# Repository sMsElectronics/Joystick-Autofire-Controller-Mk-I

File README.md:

# Joystick Auto Fire Controller V1.1
 ### This is a small form factor digitally controlled auto fire PCB with 0.1" connector headers for convenient installation into Commodore 64 and Atari Joysticks. It can be used to create custom DIY joysticks. Fire rates can be controlled using a potentiometer (analog mode) to smoothly transition from fire rate from 2 to 25 pulses per second (PPS). Alternatively, you can enter a fixed rates mode (digital Mode) with a series of button presses. The fixed rate selections are 5, 10, and 15 PPS. A normal mode is also possible by disabling the auto fire in both scenarios above. All feedback is displayed on an RGB WS2812B compatible LED and FIRE LED. Various colors and fade animation are displayed representing all the modes and rates. Further below, these modes and how to enter them are described in the illustrations

 ## *The complete and tested auto fire controller PCB's, complete with documentation, are available on my sMs Retro Electronics KoFi Shop*

## [sMs Retro Electronics KoFi Shop](https://ko-fi.com/smsretroelectronics)

 ## Size of board compared to the end of a pen.  

 ## PCB TOP VIEW

 ## PCB BOTTOM VIEW
### A convenient silkscreen showing signal names NOTE: SQUARE PIN = 1

# J2 Signal Definitions: 

|Pin Number|Signal Name|Description|
|:--:|:--:|:--|
|1|/FIRE OUT|Active low signal output that emulates the trigger into the C64 or other computer to auto fire a weapon. This signal is normally HIGH. Signal wires to pin 6 of a joystick: 
|2|FIRE_BUT|Signal from fire control button on joystick. This signal pulls LOW each time the joystick fire button is pressed. This signal is normally HIGH. :
|3|DIGRATESEL|Selects the auto fire rate. Rates of 5, 10 and 20 PPS are selectable. A Quick press cycles theSE rates. A long press FOR 1.5+ seconds enables the analog rate control|   
|4|ANA_RATE|A 0-5 VDC input from external 10K potentiometer to vary the fire rate from 2 to 23 pulses per second. This potentiometer input is only active if the joystick is set to smooth analog fire control|
|5|Fire LED-|output for user option to mount external led to indicate the press of the fire button in normal mode or to indicate auto fire pulsing in either of two auto fire modes|
|6|VCC|supply for LED+. No limiting resistor is required|
|7|DATA IN|External Neopixel RGB LED Data IN Signal|
|8|VCC|5V supply for Neopixel|
|9|GND|Ground connection for Neopixel|

# J1 Signal Definitions: 

|Pin Number|Signal Name|
|:--:|:--|
|1|5V IN|
|2|GROUND| 
   
# Summary of Modes

- Fixed Auto fire Mode
- Smooth or Analog Fire 
- Normal Mode
  
# How to Enter and Operate Each Mode

 <BR>

<BR>

# Typical application in a joystick design

# Joystick wiring details

The following diagram shows how to wire a Sanwah JLF-TP-8YT joystick , or compatible, assembly to a 9 PIN joystick cable. Some cables may be different in their color coding so its best to check continuity from each pin to the wires and identify the color verses pin. 

## If you want to DIY build your boards, the source files are available in the VS Code folder. Just keep in mind that when you create the project, inside the "libdeps" folder that contains the Tinbutton folder and TinyButton.cpp file. This file has been modifed to work with this project with the following changes. It was found that a long button press of 4 seconds was way too long and the long press woul dbe activated in 1.5 seconds instead.    

   ## Modification to file ***TinyButton.cpp*** to Shorten the LONG press criteria from 4 seconds to 1.5 seconds 
   ### W.Manganaro 2025
   
## FROM:    

      if ((currentMillis - _buttonPressTime) >= 4000)  
## TO:    

      //Value changed from 4000 to 1500 to validate a LONG press in a shorter time (approx 1.5 seconds)
      if ((currentMillis - _buttonPressTime) >= 1500)

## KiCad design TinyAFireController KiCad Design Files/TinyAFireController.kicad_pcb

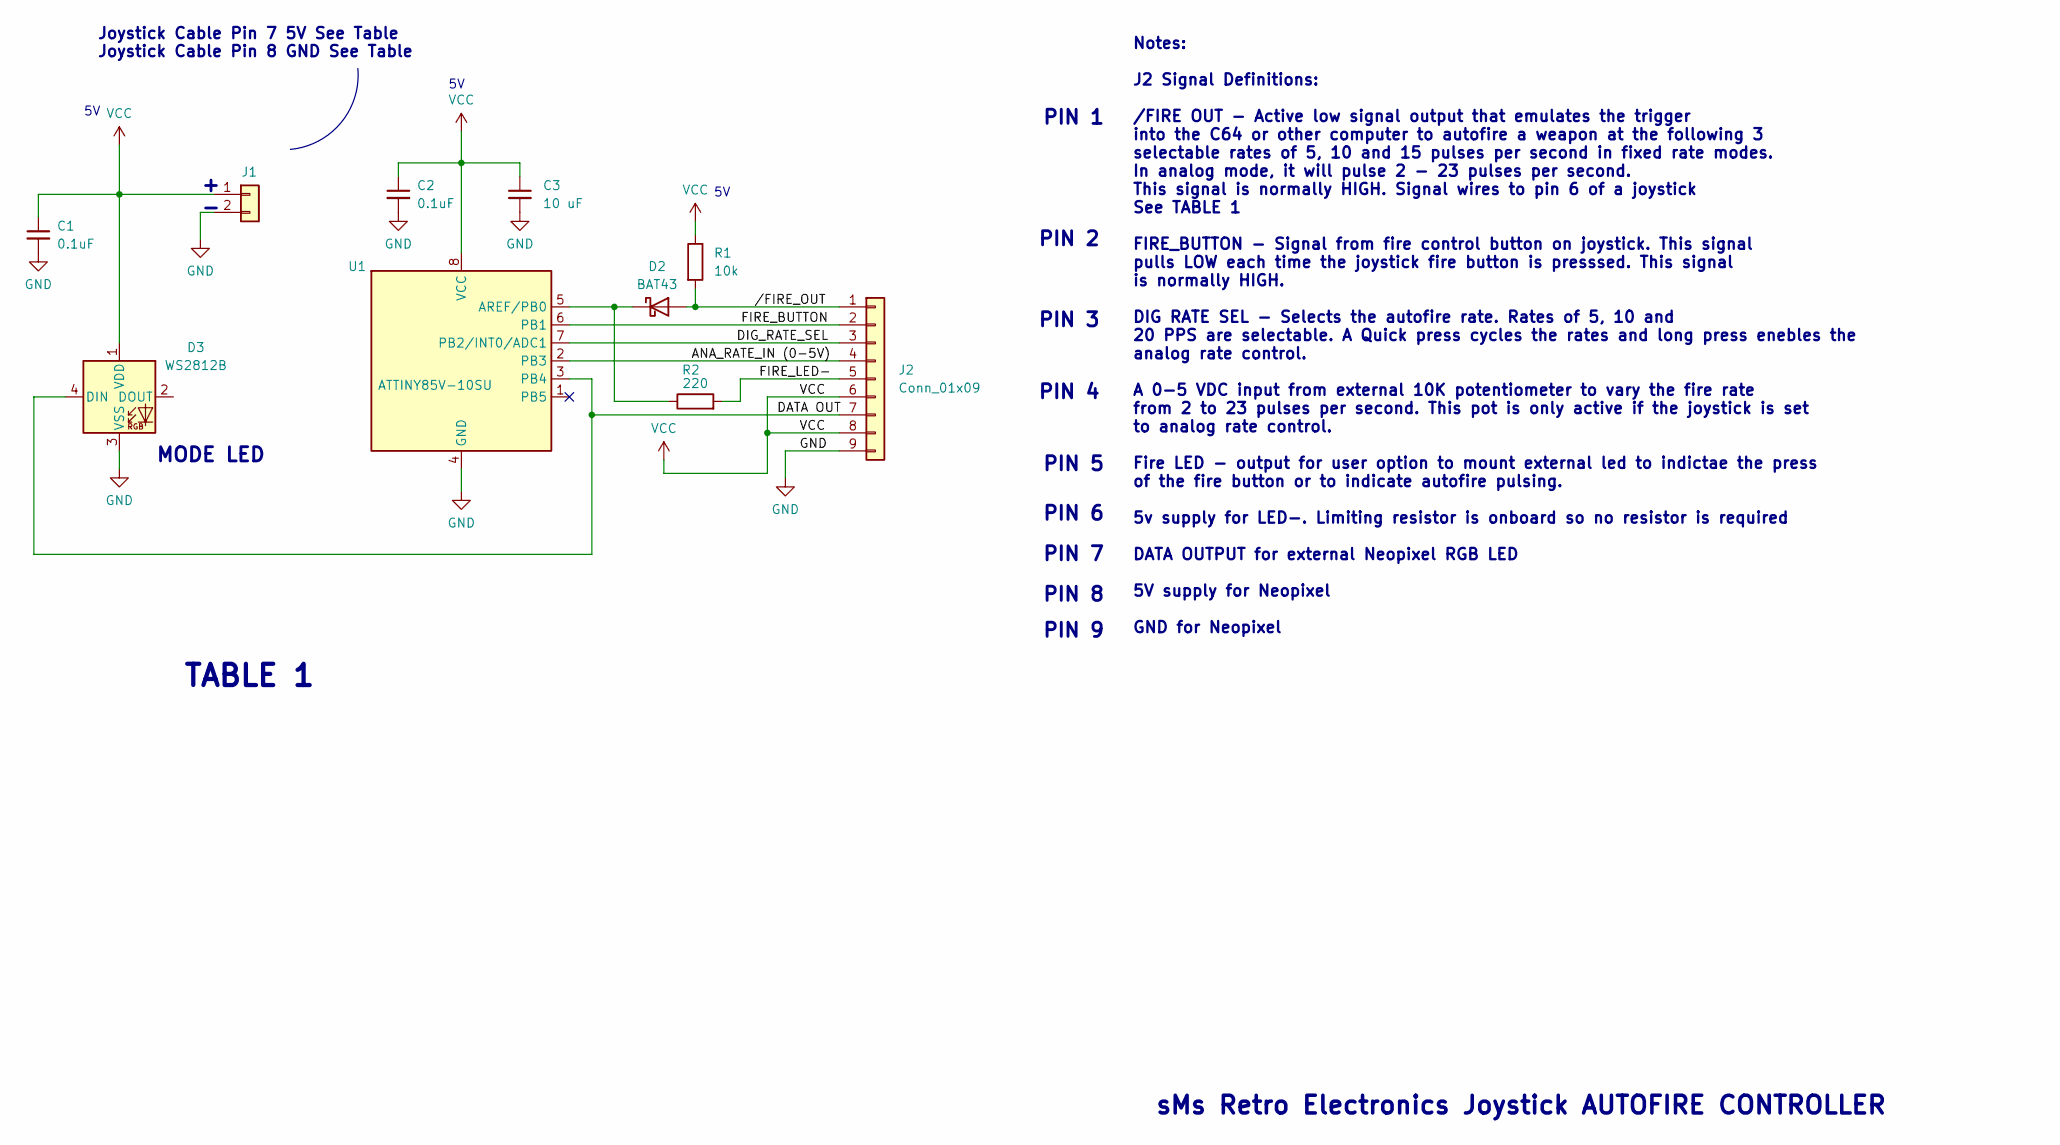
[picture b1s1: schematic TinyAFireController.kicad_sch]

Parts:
C1, C2, C3: 0.1uF_0603_16V; C_0805_2012Metric; Part Number 0603YC104KAT2A; JLCPCB ID C14663
D2: BAT43; D_SOD-123
D3: WS2812B; LED_WS2812B_PLCC4_5.0x5.0mm_P3.2mm
J1: Conn_01x02; PinHeader_1x02_P2.54mm_Horizontal; Part Number 1-0201FBV0T
J2: Conn_01x09; PinHeader_1x09_P2.54mm_Horizontal; Part Number 1-0901FBV0T
R1, R2: 100k_0603; R_0805_2012Metric; Part Number RC0603FR-07100KL; JLCPCB ID C25803
U1: ATTINY85V-10SU; SOIC-8W_5.3x5.3mm_P1.27mm

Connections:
/: D2.1 (K), R2.1, U1.5 (AREF/PB0)
/ANA_RATE_IN (0-5V): J2.4, U1.2 (PB3)
/DATA IN: D3.4 (DIN), J2.7, U1.3 (PB4)
/DIG_RATE_SEL: J2.3, U1.7 (PB2/INT0/ADC1)
/FIRE_BUTTON: J2.2, U1.6 (PB1)
/FIRE_LED-: J2.5, R2.2
//FIRE_OUT: D2.2 (A), J2.1, R1.2
GND: C1.2, C2.2, C3.2, D3.3 (VSS), J1.2, J2.9, U1.4 (GND)
VCC: C1.1, C2.1, C3.1, D3.1 (VDD), J1.1, J2.6, J2.8, R1.1, U1.8 (VCC)

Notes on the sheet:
TABLE 1
PIN 5
Joystick Cable Pin 7 5V See Table
PIN 7
PIN 1
PIN 3
PIN 6
sMs Retro Electronics Joystick AUTOFIRE CONTROLLER
MODE LED
PIN 8
Notes: J2 Signal Definitions: /FIRE OUT - Active low signal output that emulates the trigger into the C64 or other computer to autofire a weapon at the following 3 selectable rates of 5, 10 and 15 pulses per second in fixed rate modes. In analog mode, it will pulse 2 - 23 pulses per second. This si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
Joystick Cable Pin 8 GND See Table
PIN 4
PIN 2
PIN 9

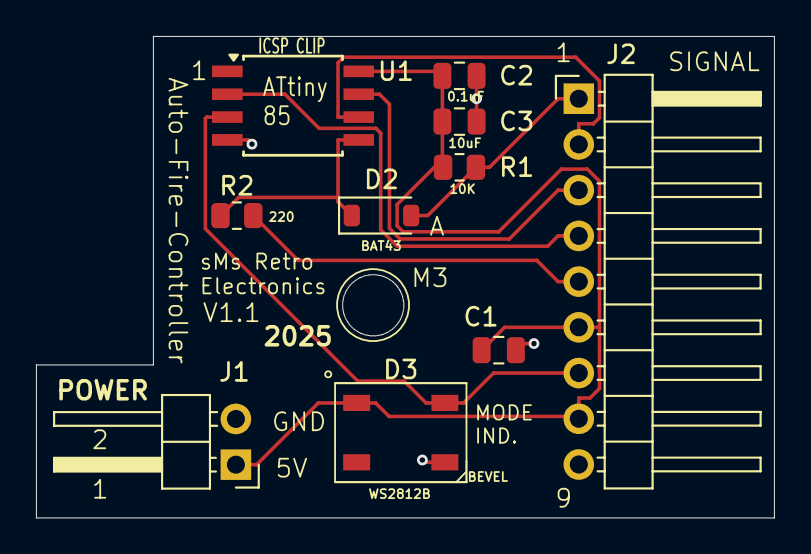
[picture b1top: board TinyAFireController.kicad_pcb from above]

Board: 2 copper layers, 41.0 x 26.8 mm, 10 parts (0 on the bottom side), 9 nets.

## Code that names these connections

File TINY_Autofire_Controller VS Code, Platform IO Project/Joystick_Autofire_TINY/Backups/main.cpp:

/* sMs Retro Electronics
   Joystick Autofire Controller 
   Author: William Manganaro 2024
*/

#include <Arduino.h>
#include <TinyButton.h>
// #include <FastLED.h>

// pin defines
#define DIG_RATE_SEL 2
#define FIRE_OUT 0
#define FIRE_BUTTON 1

// variables
bool analog_rate_flag = false; // if this is false, then fixed rate controls are used
bool autofire_enable_flag = false; // when flag is true, autofire is enabled.
int ana_rate_in = A3;   // select the input pin for the potentiometer
int rateValue; // analog autofire rate vale scaled from 2 to 25 pulses per second
byte mode_counter = 0; // mode counter will span 0-2 that represent three spped variables. 
// init the fire rate to the lowest to 5 pulse per second
// 0 = 5 pps 1 = 10 pps 2 = 15 pps
int delay_val[] = {250,167,125,100,84,72,63,56,50,46,42,39,36,33,31,29,27,26,25,24,23,22,21,20}; // pps = 1/(2*delay_val(n)) where n= eleement of array in milliseconds
TinyButton myButton(DIG_RATE_SEL); // create the object myButton on port b.2 and name the button myButton

// functions

// read a/d potentiometer and scale the rate to 2 - 20 pps
void Read_Analog_Rate_Potentiometer() {
    rateValue = analogRead(ana_rate_in); // read a/d conv
    rateValue = map(rateValue, 0, 1023, 0, 23); // scale a/d value to a range of autorate vales from 0-1023 to 2-20 PPS
}
// Function that is triggered by a normal click
void mode_change_fixed_rates() {
    digitalWrite(FIRE_OUT, LOW); // turn test led on
  if (!analog_rate_flag) // mode_counter counts 0-1-2-0-1-2- etc if the analog rate flag is FALSE
    {
        mode_counter++;
   if (mode_counter==3)
  {
    mode_counter=0;
  }
    }
}

// Function that is triggered by a long click
// if this flag is TRUE, then rate control is input from the analog input 
// if the flag is FALSE then the control is handed to the DIG_RATE_SEL input
void analog_rate_control_enable() {
      digitalWrite(FIRE_OUT, HIGH); // turn test led off
      analog_rate_flag = !analog_rate_flag; // toggle the flag 
}


void setup() {
    myButton.attachClick(mode_change_fixed_rates); // This is the function for the normal click
    myButton.attachLongClick(analog_rate_control_enable);   // This is the function for the long click
    pinMode(5,OUTPUT); // port b pin 5 is not used but is still prudent o define a state
    digitalWrite(5, HIGH); // init the portb.5 output to logic high
    pinMode(FIRE_OUT, OUTPUT); // define the fire output signal (active low)
    digitalWrite(FIRE_OUT, HIGH); // init the fire output signal to logic high
    pinMode(FIRE_BUTTON, INPUT); // fire button input 
    pinMode(DIG_RATE_SEL, INPUT); // digital rate select input 
    PORTB |= (1 << PB1 | 1 << PB2);  //activate pull-up resistor for PB1 & PB2 inputs


}

void loop() {
 myButton.tick();
 while (digitalRead (FIRE_BUTTON)==LOW && autofire_enable_flag==false)
{
   digitalWrite(FIRE_OUT, LOW); 
   delay(25);
   digitalWrite(FIRE_OUT, HIGH); 
   delay(25);
}

}

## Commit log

2024-12-29 First Commit
    Added the Kicad Design Files
2025-01-21 Added to Kicad
    SCH PDF and Gerber V1.1
2025-01-21 Create Change to TinyButton.cpp .txt
    added readme file
2025-01-27 Numerious changes for first publish
    added many files to repository and created readme.md file.
2025-01-29 Update README.md
    Added Tables
2025-01-29 Update LICENSE
    Changed LICENSE to MIT
2025-01-29 Added BOM
    Created a BOM.md file
    Corrected wrong resistor values for R1 and R2
2025-01-29 Create README.md
    Changed the name from BOM.md to README.md so that the BOM appears as a table automatically.
2025-01-29 Deleted BOM.md
    Deleted file because it is not required
2025-02-01 Update README.md
    Added notes on what needs to be modified in the TinyButton library in order for the long button press to work within a reasonable time.
